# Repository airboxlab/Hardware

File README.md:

# Airboxlab Hardware
Documentation, electronics and mechanical CAD for Airboxlab

* Consult Bills of Materials available in this repo, for the diferent parts needed.
* Assembly instructions available in this repo in [html](https://cdn.rawgit.com/airboxlab/Hardware/master/Assembly_Instructions/assembly_instructions.html).
* Firmware documentation is in the [wiki](https://github.com/airboxlab/Firmware/wiki).

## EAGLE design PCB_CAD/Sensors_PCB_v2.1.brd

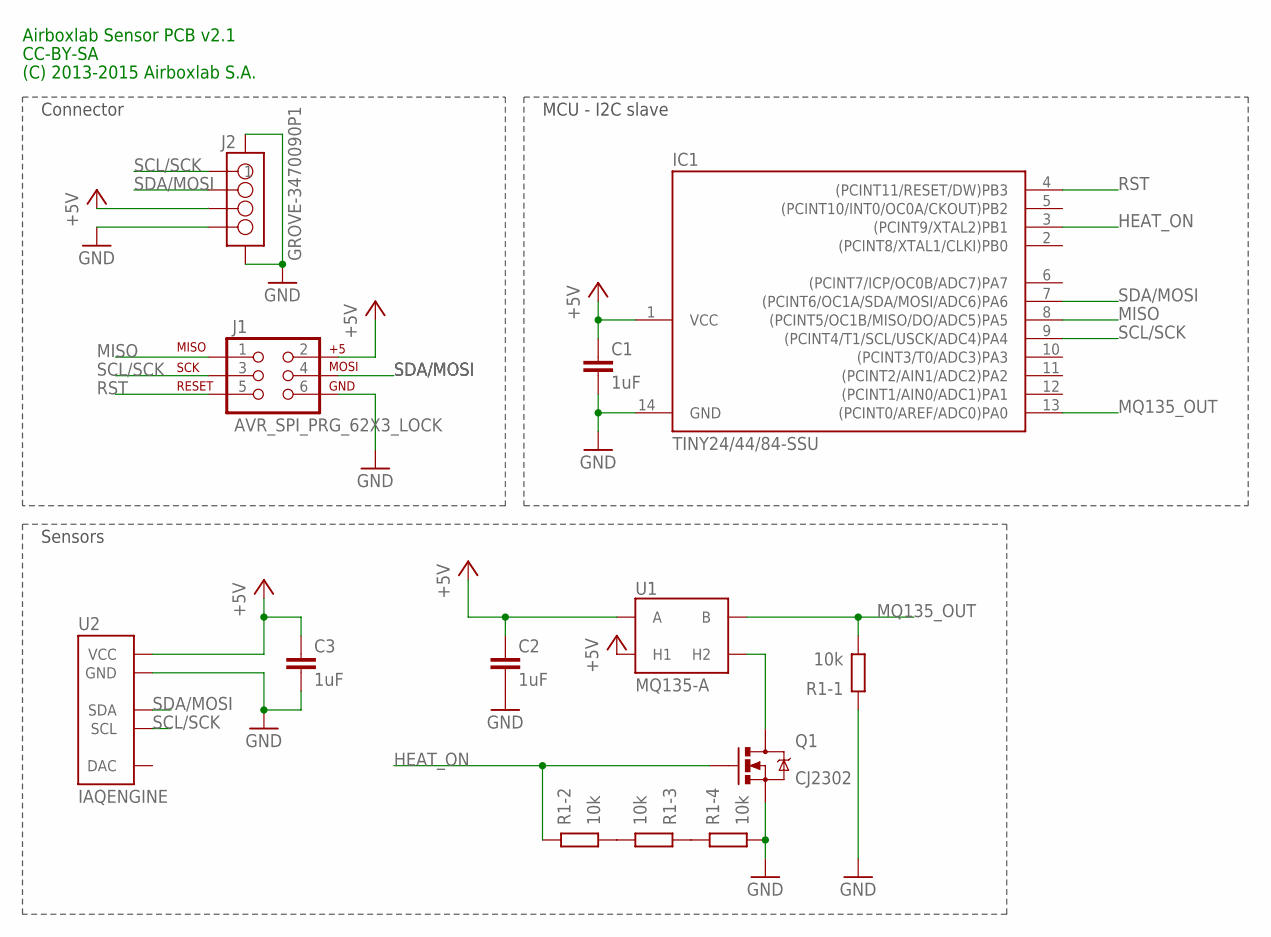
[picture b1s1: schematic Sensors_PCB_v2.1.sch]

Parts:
C1, C2, C3: 1uF; 0603_N
IC1: TINY24/44/84-SSU; SOIC14
J1: AVR_SPI_PRG_62X3_LOCK; 2X3_LOCK
J2: GROVE-3470090P1; 4P-SMD-2.0
Q1: CJ2302; SOT-23-3_N/SSOT-3_N
R1: 10k; R_0603_80P_4
U1: MQ135-A
U2: IAQENGINE

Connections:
+5V: C1.1, C2.1, C3.1, IC1.1 (VCC), J1.2, J2.3, U1.1 (A), U1.2 (H1), U1.3 (A), U2.6 (VCC)
GND: C1.2, C2.2, C3.2, IC1.14 (GND), J1.6, J2.4, J2.SS1, J2.SS2, Q1.2 (S), R1.4 (1), R1.8 (2), U2.3 (GND)
HEAT_ON: IC1.3 ((PCINT9/XTAL2)PB1), Q1.1 (G), R1.7 (2)
MISO: IC1.8 ((PCINT5/OC1B/MISO/DO/ADC5)PA5), J1.1
MQ135_OUT: IC1.13 ((PCINT0/AREF/ADC0)PA0), R1.1, U1.4 (B), U1.6 (B)
unnamed: R1.5 (2), R1.6 (2)
unnamed: R1.2 (1), R1.3 (1)
unnamed: Q1.3 (D), U1.5 (H2)
RST: IC1.4 ((PCINT11/RESET/DW)PB3), J1.5
SCL/SCK: IC1.9 ((PCINT4/T1/SCL/USCK/ADC4)PA4), J1.3, J2.1, U2.2 (SCL)
SDA/MOSI: IC1.7 ((PCINT6/OC1A/SDA/MOSI/ADC6)PA6), J1.4, J2.2, U2.4 (SDA)

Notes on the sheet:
Sensors
Connector
MCU - I2C slave
(C) 2013-2015 Airboxlab S.A.
CC-BY-SA
Airboxlab Sensor PCB v2.1

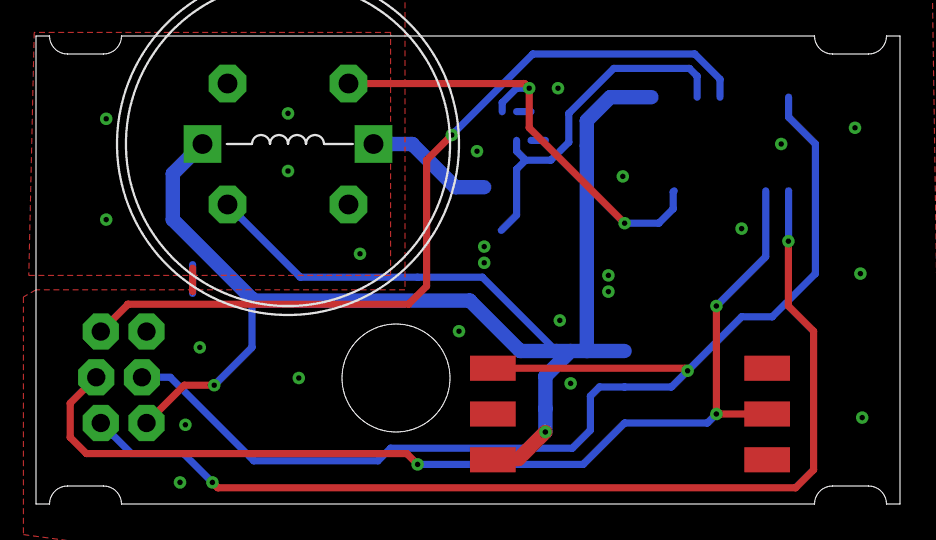
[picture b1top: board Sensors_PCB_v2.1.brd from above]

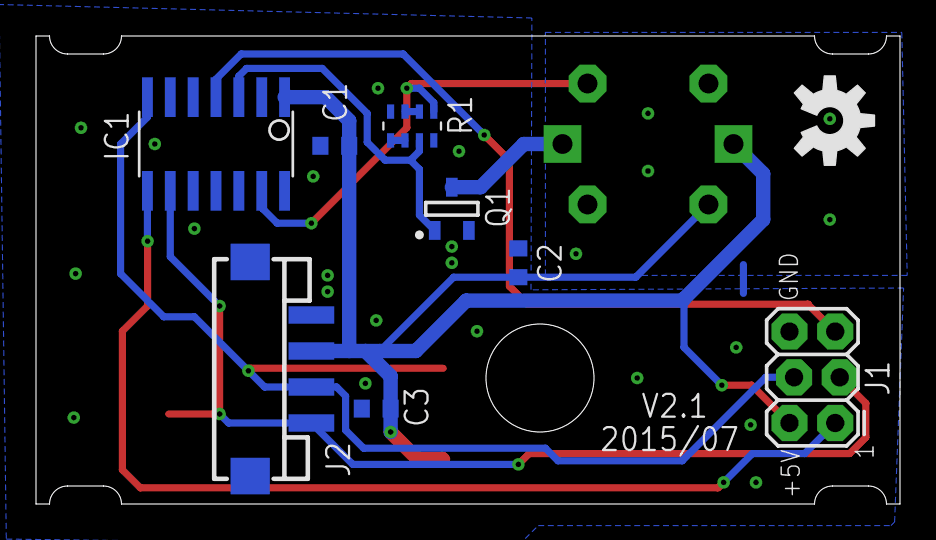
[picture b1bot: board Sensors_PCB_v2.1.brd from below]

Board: 2 copper layers, 48.0 x 26.0 mm, 11 parts (9 on the bottom side), 11 nets.

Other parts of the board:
U$1: OSHW-LOGO-M

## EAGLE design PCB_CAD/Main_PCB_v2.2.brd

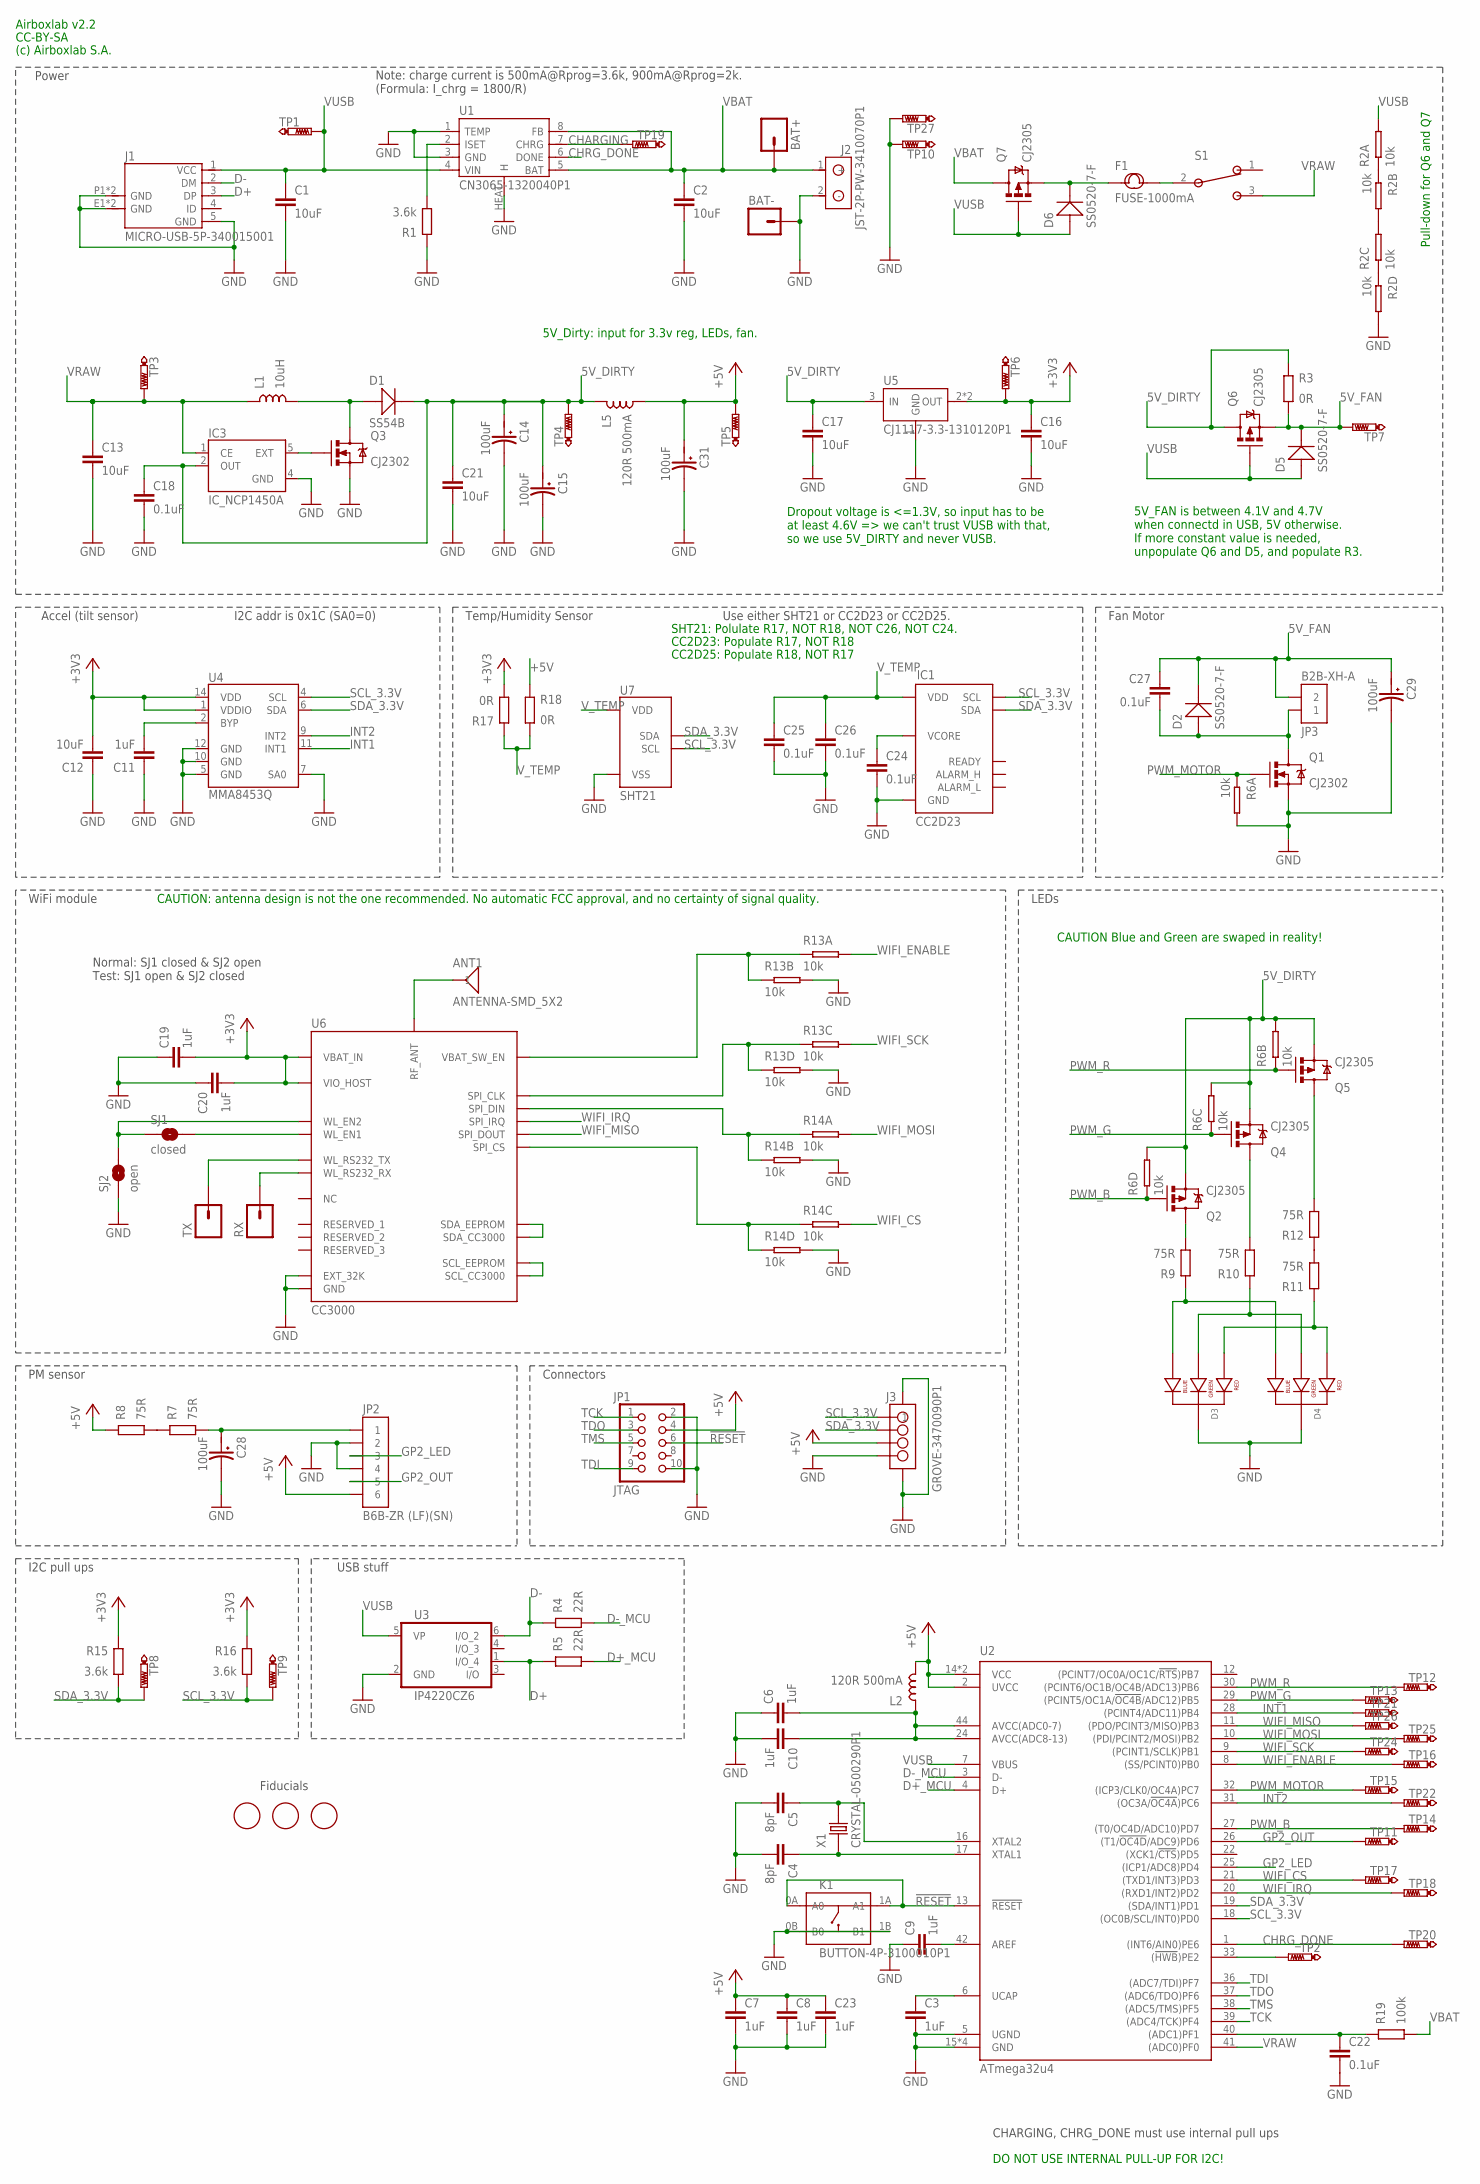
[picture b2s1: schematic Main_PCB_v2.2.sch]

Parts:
ANT1: ANTENNA-SMD_5X2; ANTENNA_SMD_5X2
BAT+: M01PTH; 1X01
BAT-: M01PTH; 1X01
C1, C2, C12, C13, C16, C17, C21: 10uF; 0805_N
C3, C6, C7, C8, C9, C10, C11, C19, C20, C23: 1uF; 0603_N
C4, C5: 8pF; 0603_N
C14, C15, C28, C29, C31: 100uF; AVX-C
C18, C22, C24, C25, C26, C27: 0.1uF; 0603_N
D1: SS54B; SMB
D2, D5, D6: SS0520-7-F; SOD123
D3, D4: LED-RGB-CC-THRUCLEAR; LED-RGB-THRU
F1: FUSE-1000mA; F1206
IC1: CC2D23; CC2DXX
IC3: IC_NCP1450A; SOT-23-5_N
J1: MICRO-USB-5P-340015001; B-SMD-5P
J2: JST-2P-PW-3410070P1; 2P-2.0-90D
J3: GROVE-3470090P1; 4P-SMD-2.0
JP1: JTAG; CONNECTOR_2.54MM_5X2_LOCK
JP2: B6B-ZR (LF)(SN); CONNECTOR_B6B-ZR
JP3: B2B-XH-A; CONNECTOR_B2B-XH-A
K1: BUTTON-4P-3100010P1; 4P-SMD-6.0X6.0X5.0H
L1: 10uH; L_SRU8043
L2, L5: 120R 500mA; 0603_N
Q1, Q3: CJ2302; SOT-23-3_N/SSOT-3_N
Q2, Q4, Q5, Q6, Q7: CJ2305; SOT-23-3_N/SSOT-3_N
R1, R15, R16: 3.6k; 0603_N
R2, R6, R13, R14: 10k; R1206-8
R3, R17, R18: 0R; 0603_N
R4, R5: 22R; 0603_N
R7, R8, R9, R10, R11, R12: 75R; 0603_N
R19: 100k; 0603_N
RX: M01PTH; 1X01
S1: SWITCH_SPDT_ON-ON; SWITCH_SPDT_OS102011MA1QN1
SJ1: closed; SJ_2S-TRACE2
SJ2: open; SJ_2S-NO
TP1, TP3, TP4, TP5, TP6, TP7, TP8, TP9, TP10, TP11: PTR1PAD1-13; P1-13
TP2, TP12, TP13, TP14, TP15, TP16, TP17, TP18, TP19, TP20, TP21, TP22, TP24, TP25, TP26: PTR1B1,27; B1,27
TP27: PTR1PAD1-13Y; P1-13Y
TX: M01PTH; 1X01
U1: CN3065-1320040P1; DFN8
U2: ATmega32u4; QFN-44_50P_N
U3: IP4220CZ6; SOT95P275X110-6N
U4: MMA8453Q; QFN-16_0.5MM
U5: CJ1117-3.3-1310120P1; SOT89
U6: CC3000
U7: SHT21; SHT2X
U$1, U$2, U$3: FIDUCIAL; FIDUCIAL_1MM
X1: CRYSTAL-0500290P1; 2P-SMD-5.0X3.2

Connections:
5V_DIRTY: C14.+ (1), C15.+ (1), C17.1, C18.1, C21.1, D1.-, IC3.2 (OUT), L5.1, Q2.2 (S), Q4.2 (S), Q5.2 (S), Q6.3 (D), R3.2, R6.5 (2), R6.6 (2), R6.7 (2), TP4.TP, U5.3 (IN)
5V_FAN: C27.1, C29.+ (1), D2.-, D5.-, JP3.2, Q6.2 (S), R3.1, TP7.TP
!RESET!: JP1.6, K1.0A (A0), K1.1A (A1), U2.13 (!RESET!)
+3V3: C12.2, C16.1, C19.2, C20.2, R15.2, R16.2, R17.1, TP6.TP, U4.1 (VDDIO), U4.14 (VDD), U5.2 (OUT), U5.4 (OUT), U6.P$19 (VBAT_IN), U6.P$23 (VIO_HOST)
+5V: C7.1, C8.1, C23.1, C31.+ (1), J3.3, JP1.4, JP2.P$6 (6), L2.2, L5.2, R8.2, R18.2, TP5.TP, U2.2 (UVCC), U2.14 (VCC), U2.34 (VCC)
CHARGING: TP19.TP, U1.7 (CHRG)
CHRG_DONE: TP20.TP, U1.6 (DONE), U2.1 ((INT6/AIN0)PE6)
D+: J1.3 (DP), R5.2, U3.1 (I/O_4)
D+_MCU: R5.1, U2.4 (D+)
D-: J1.2 (DM), R4.2, U3.6 (I/O_2)
D-_MCU: R4.1, U2.3 (D-)
GND: BAT-.1, C1.2, C2.2, C3.2, C4.2, C5.2, C6.1, C7.2, C8.2, C9.1, C10.2, C11.1, C12.1, C13.2, C14.- (2), C15.- (2), C16.2, C17.2, C18.2, C19.1, C20.1, C21.2, C22.2, C23.2, C24.2, C25.2, C26.2, C28.- (2), C29.- (2), C31.- (2), D3.2 (CATHODE), D4.2 (CATHODE), IC1.P$6 (GND), IC3.4 (GND), J1.5 (GND), J1.E1 (GND), J1.E2 (GND), J1.P1 (GND), J1.P2 (GND), J2.2 (-), J3.4, J3.SS1, J3.SS2, JP1.2, JP1.10, JP2.P$2 (2), JP2.P$4 (4), K1.0B (B0), K1.1B (B1), Q1.2 (S), Q3.2 (S), R1.2, R2.5 (2), R6.8 (2), R13.5 (2), R13.7 (2), R14.5 (2), R14.7 (2), SJ2.1, TP10.TP, TP27.TP, U1.1 (TEMP), U1.3 (GND), U1.HEAT (H), U2.5 (UGND), U2.15 (GND), U2.23 (GND), U2.35 (GND), U2.43 (GND), U3.2 (GND), U4.5 (GND), U4.7 (SA0), U4.10 (GND), U4.12 (GND), U5.1 (GND), U6.P$1 (GND), U6.P$9 (GND), U6.P$10 (GND), U6.P$11 (GND), U6.P$16 (GND), U6.P$18 (GND), U6.P$20 (GND), U6.P$21 (EXT_32K), U6.P$22 (GND), U6.P$25 (GND), U6.P$31 (GND), U6.P$32 (GND), U6.P$33 (GND), U6.P$34 (GND), U6.P$36 (GND), U6.P$37 (GND), U6.P$38 (GND), U6.P$39 (GND), U6.P$40 (GND), U6.P$41 (GND), U6.P$42 (GND), U6.P$43 (GND), U6.P$44 (GND), U6.P$45 (GND), U6.P$46 (GND), U7.0 (VSS), U7.2 (VSS)
GP2_LED: JP2.P$3 (3), U2.25 ((ICP1/ADC8)PD4)
GP2_OUT: JP2.P$5 (5), TP11.TP, U2.26 ((T1/!OC4D!/ADC9)PD6)
INT1: TP21.TP, U2.28 ((PCINT4/ADC11)PB4), U4.11 (INT1)
INT2: TP22.TP, U2.31 ((OC3A/!OC4A!)PC6), U4.9 (INT2)
unnamed: R1.1, U1.2 (ISET)
unnamed: D6.-, F1.1, Q7.2 (S)
unnamed: D1.+, L1.P$2 (2), Q3.3 (D)
unnamed: C11.2, U4.2 (BYP)
unnamed: C3.1, U2.6 (UCAP)
unnamed: C4.1, U2.17 (XTAL1), X1.1
unnamed: C5.1, U2.16 (XTAL2), X1.2
unnamed: C6.2, C10.1, L2.1, U2.24 (AVCC(ADC8-13)), U2.44 (AVCC(ADC0-7))
unnamed: IC3.5 (EXT), Q3.1 (G)
unnamed: U6.P$27 (SDA_EEPROM), U6.P$28 (SDA_CC3000)
unnamed: C9.2, U2.42 (AREF)
unnamed: F1.2, S1.2
unnamed: R2.1, R2.2 (1)
unnamed: R2.6 (2), R2.7 (2)
unnamed: R2.3 (1), R2.4 (1)
unnamed: U6.P$29 (SCL_EEPROM), U6.P$30 (SCL_CC3000)
unnamed: Q5.3 (D), R12.1
unnamed: Q4.3 (D), R10.1
unnamed: Q2.3 (D), R9.1
unnamed: C27.2, D2.+, JP3.1, Q1.3 (D)
unnamed: C28.+ (1), JP2.P$1 (1), R7.1
unnamed: C22.1, R19.2, U2.40 ((ADC1)PF1)
unnamed: R7.2, R8.1
unnamed: C24.1, IC1.P$5 (VCORE)
unnamed: TX.1, U6.P$6 (WL_RS232_TX)
unnamed: SJ1.2, U6.P$7 (WL_EN1)
unnamed: SJ1.1, SJ2.2, U6.P$5 (WL_EN2)
unnamed: RX.1, U6.P$8 (WL_RS232_RX)
unnamed: ANT1.1, U6.P$35 (RF_ANT)
unnamed: D3.4 (BLUE_CATHODE), D4.4 (BLUE_CATHODE), R9.2
unnamed: D3.3 (GREEN_CATHODE), D4.3 (GREEN_CATHODE), R10.2
unnamed: R11.1, R12.2
unnamed: D3.1 (RED_CATHODE), D4.1 (RED_CATHODE), R11.2
unnamed: R14.3 (1), R14.4 (1), U6.P$12 (SPI_CS)
unnamed: R14.1, R14.2 (1), U6.P$15 (SPI_DIN)
unnamed: R13.3 (1), R13.4 (1), U6.P$17 (SPI_CLK)
unnamed: R13.1, R13.2 (1), U6.P$26 (VBAT_SW_EN)
unnamed: TP2.TP, U2.33 ((!HWB!)PE2)
PWM_B: Q2.1 (G), R6.4 (1), TP14.TP, U2.27 ((T0/OC4D/ADC10)PD7)
PWM_G: Q4.1 (G), R6.3 (1), TP13.TP, U2.29 ((PCINT5/OC1A/!OC4B!/ADC12)PB5)
PWM_MOTOR: Q1.1 (G), R6.1, TP15.TP, U2.32 ((ICP3/CLK0/OC4A)PC7)
PWM_R: Q5.1 (G), R6.2 (1), TP12.TP, U2.30 ((PCINT6/OC1B/OC4B/ADC13)PB6)
SCL_3.3V: IC1.P$4 (SCL), J3.1, R16.1, TP9.TP, U2.18 ((OC0B/SCL/INT0)PD0), U4.4 (SCL), U7.6 (SCL)
SDA_3.3V: IC1.P$3 (SDA), J3.2, R15.1, TP8.TP, U2.19 ((SDA/INT1)PD1), U4.6 (SDA), U7.1 (SDA)
TCK: JP1.1, U2.39 ((ADC4/TCK)PF4)
TDI: JP1.9, U2.36 ((ADC7/TDI)PF7)
TDO: JP1.3, U2.37 ((ADC6/TDO)PF6)
TMS: JP1.5, U2.38 ((ADC5/TMS)PF5)
VBAT: BAT+.1, C2.1, J2.1 (+), Q7.3 (D), R19.1, U1.5 (BAT), U1.8 (FB)
VRAW: C13.1, IC3.1 (CE), L1.P$1 (1), S1.3, TP3.TP, U2.41 ((ADC0)PF0)
VUSB: C1.1, D5.+, D6.+, J1.1 (VCC), Q6.1 (G), Q7.1 (G), R2.8 (2), TP1.TP, U1.4 (VIN), U2.7 (VBUS), U3.5 (VP)
V_TEMP: C25.1, C26.1, IC1.P$7 (VDD), R17.2, R18.1, U7.5 (VDD)
WIFI_CS: R14.6 (2), TP17.TP, U2.21 ((TXD1/INT3)PD3)
WIFI_ENABLE: R13.8 (2), TP16.TP, U2.8 ((SS/PCINT0)PB0)
WIFI_IRQ: TP18.TP, U2.20 ((RXD1/INT2)PD2), U6.P$14 (SPI_IRQ)
WIFI_MISO: TP26.TP, U2.11 ((PDO/PCINT3/MISO)PB3), U6.P$13 (SPI_DOUT)
WIFI_MOSI: R14.8 (2), TP25.TP, U2.10 ((PDI/PCINT2/MOSI)PB2)
WIFI_SCK: R13.6 (2), TP24.TP, U2.9 ((PCINT1/SCLK)PB1)

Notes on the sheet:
Power
Note: charge current is 500mA@Rprog=3.6k, 900mA@Rprog=2k. (Formula: I_chrg = 1800/R)
CHARGING, CHRG_DONE must use internal pull ups
Connectors
WiFi module
USB stuff
I2C addr is 0x1C (SA0=0)
Accel (tilt sensor)
Normal: SJ1 closed & SJ2 open Test: SJ1 open & SJ2 closed
SHT21: Polulate R17, NOT R18, NOT C26, NOT C24.
Temp/Humidity Sensor
Use either SHT21 or CC2D23 or CC2D25.
Fan Motor
5V_Dirty: input for 3.3v reg, LEDs, fan.
PM sensor
LEDs
CAUTION: antenna design is not the one recommended. No automatic FCC approval, and no certainty of signal quality.
DO NOT USE INTERNAL PULL-UP FOR I2C!
I2C pull ups
CAUTION Blue and Green are swaped in reality!
Dropout voltage is <=1.3V, so input has to be at least 4.6V => we can't trust VUSB with that, so we use 5V_DIRTY and never VUSB.
5V_FAN is between 4.1V and 4.7V when connectd in USB, 5V otherwise. If more constant value is needed, unpopulate Q6 and D5, and populate R3.
Pull-down for Q6 and Q7
Fiducials
CC2D23: Populate R17, NOT R18
CC2D25: Populate R18, NOT R17
Airboxlab v2.2
CC-BY-SA
(c) Airboxlab S.A.

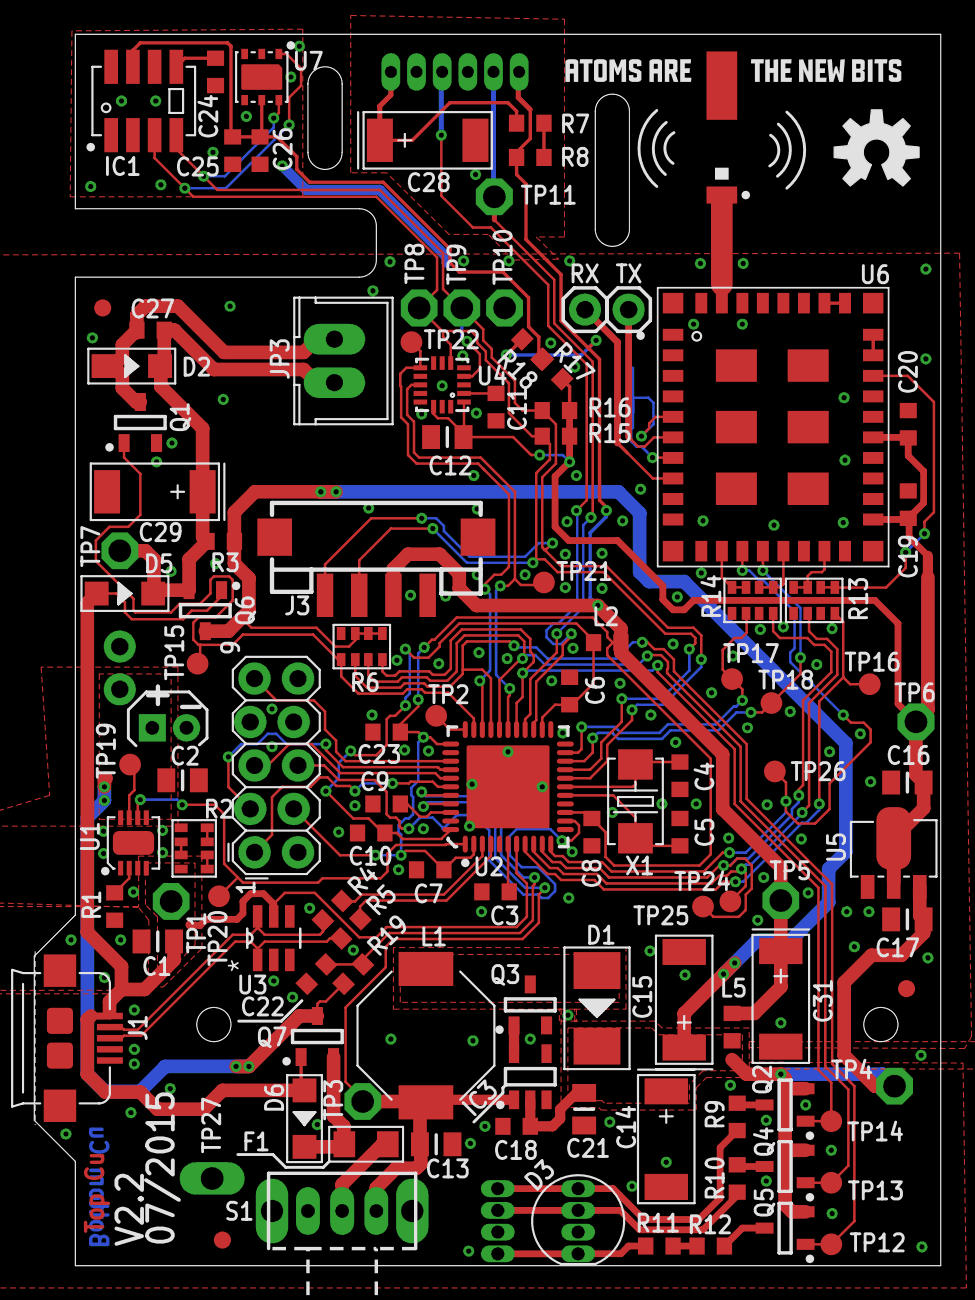
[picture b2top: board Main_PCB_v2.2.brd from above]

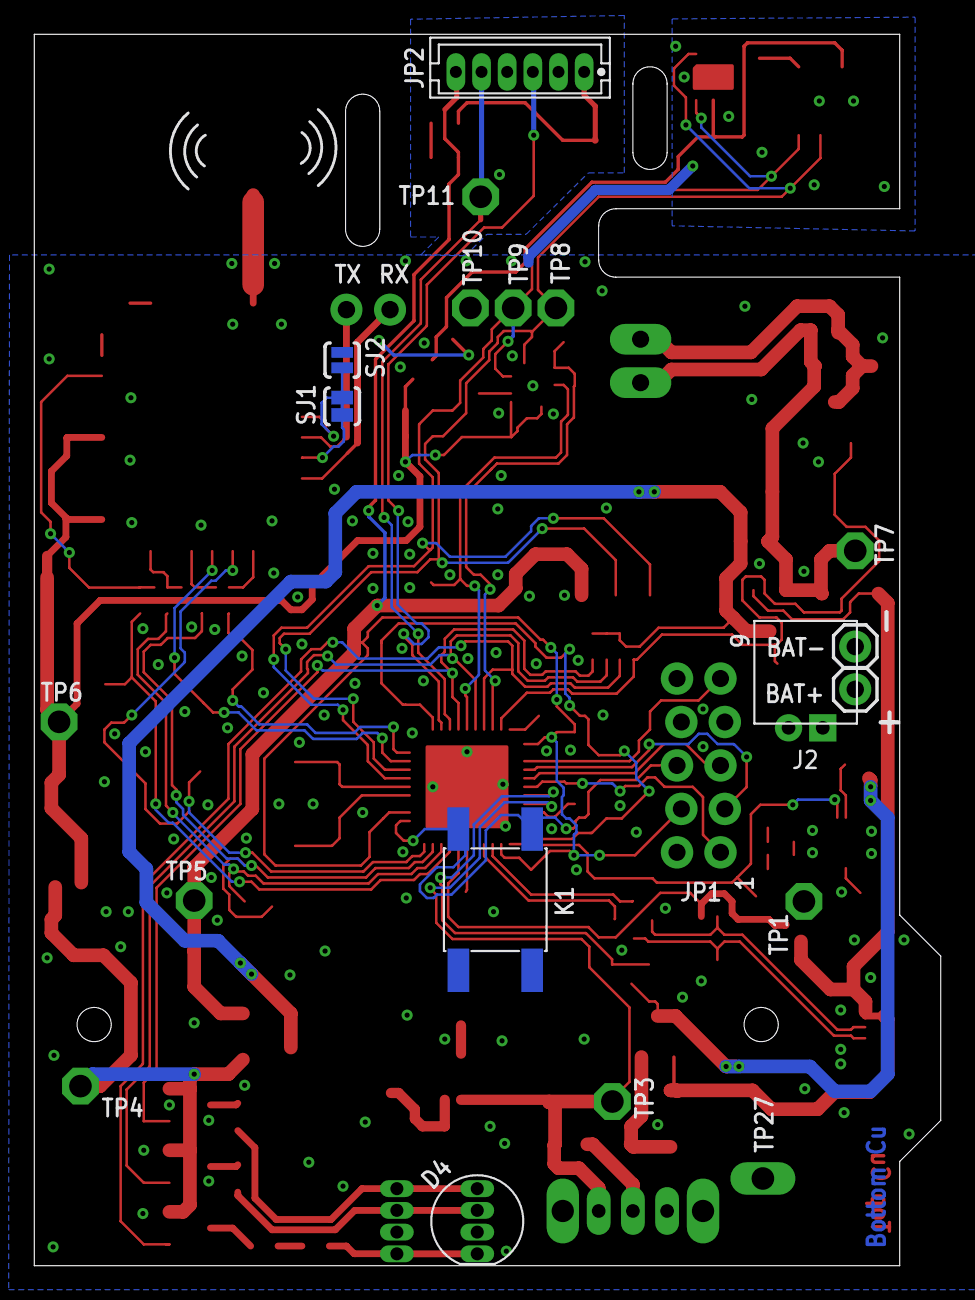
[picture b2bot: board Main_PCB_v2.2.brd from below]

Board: 2 copper layers, 53.0 x 72.0 mm, 121 parts (9 on the bottom side), 74 nets.

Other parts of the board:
U$4: OSHW-LOGO-M

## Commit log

2015-07-28 add readme
2015-08-10 add missing sensor to BOM

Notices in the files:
parts and their libraries:
SparkFun-Connectors: Licensing: CC v3.0 Share-Alike You are welcome to use this library for commercial purposes.
SparkFun-Aesthetics: Licensing: Creative Commons ShareAlike 4.0 International - https://creativecommons.org/licenses/by-sa/4.0
